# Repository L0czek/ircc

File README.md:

# Resonant Converter Controller

This repository contains a work-in-progress resonant converter controller project based on the STM32G474 microcontroller. The system splits responsibilities between the MCU (`controller`) and a host application (`host`) running on an x86 machine for configuration, logging, and waveform retrieval.

**Goals**
- Implement a phase-shifted resonant converter controller using the STM32G474 high-resolution timers.
- Provide over-current and other protections using built-in ADCs and comparator peripherals.
- Log waveforms to local SRAM for later retrieval by the host.
- Provide a PC-side host binary to configure and interact with the MCU.

Repository layout
- [controller](controller): MCU firmware (STM32 HAL-based). Core control logic lives here.
- [host](host): Host-side application that communicates with the MCU (x86 binary).
- [target](target): CubeMX / board-specific projects and HAL integration for different targets/boards.
- [pcb](pcb): KiCad PCB design files for the controller hardware.
- [protocol](protocol): Protocol definitions and protobufs used by host/MCU.
- [external](external): Third-party libraries and dependencies (e.g., nanpb, drivers).
- [build](build): Top-level build artifacts and CMake cache (generated during builds).

Quick start

Build host part (x86):

1. Enter the host directory and create a build directory:

```bash
cd host
mkdir -p build && cd build
cmake ..
make -j
```

The produced host binary will be in `host/build` (or as specified by the host CMakeLists).

Build MCU firmware:

1. Edit or inspect the CubeMX project in the appropriate `target/*` folder (for your chosen board). Generate code from CubeMX if you modify pin/peripheral configuration.
2. Use CMake from the top-level CMake to build the firmware. Example (from project root):

```bash
mkdir -p build-mcu && cd build-mcu
cmake -DCMAKE_TOOLCHAIN_FILE=cmake/gcc-arm-none-eabi.cmake ..
make -j
```

Flashing and debugging
- An OpenOCD config is available at `build/openocd.cfg` for target debugging.
- Typical workflow using the repository make targets:

	1. Start OpenOCD to provide the debug server:

		 ```bash
		 make openocd
		 ```

	2. In a separate terminal, flash or debug the firmware:

		 - To flash and run the firmware:

			 ```bash
			 make run
			 ```

		 - To spawn `gdb` for interactive debugging (connects to the OpenOCD server):

			 ```bash
			 make gdb
			 ```

- Or use your preferred OpenOCD/ST-Link workflow if you have a different setup.

Protocol and message formats
- Communication between host and MCU uses a UART serial link and the message definitions in the [protocol](protocol) directory (protobuf/nanopb). Regenerate or inspect generated code if you change `.proto` files.

Design notes
- The controller firmware uses the STM32G474 high-resolution timers to implement phase-shift control for MOSFET/IGBT bridge switching.
- ADCs, comparators, and timers are used for protections, sampling, and logging to SRAM.

Acknowledgements
- Third-party libraries are located in `external/` — see their respective LICENSE files for details.

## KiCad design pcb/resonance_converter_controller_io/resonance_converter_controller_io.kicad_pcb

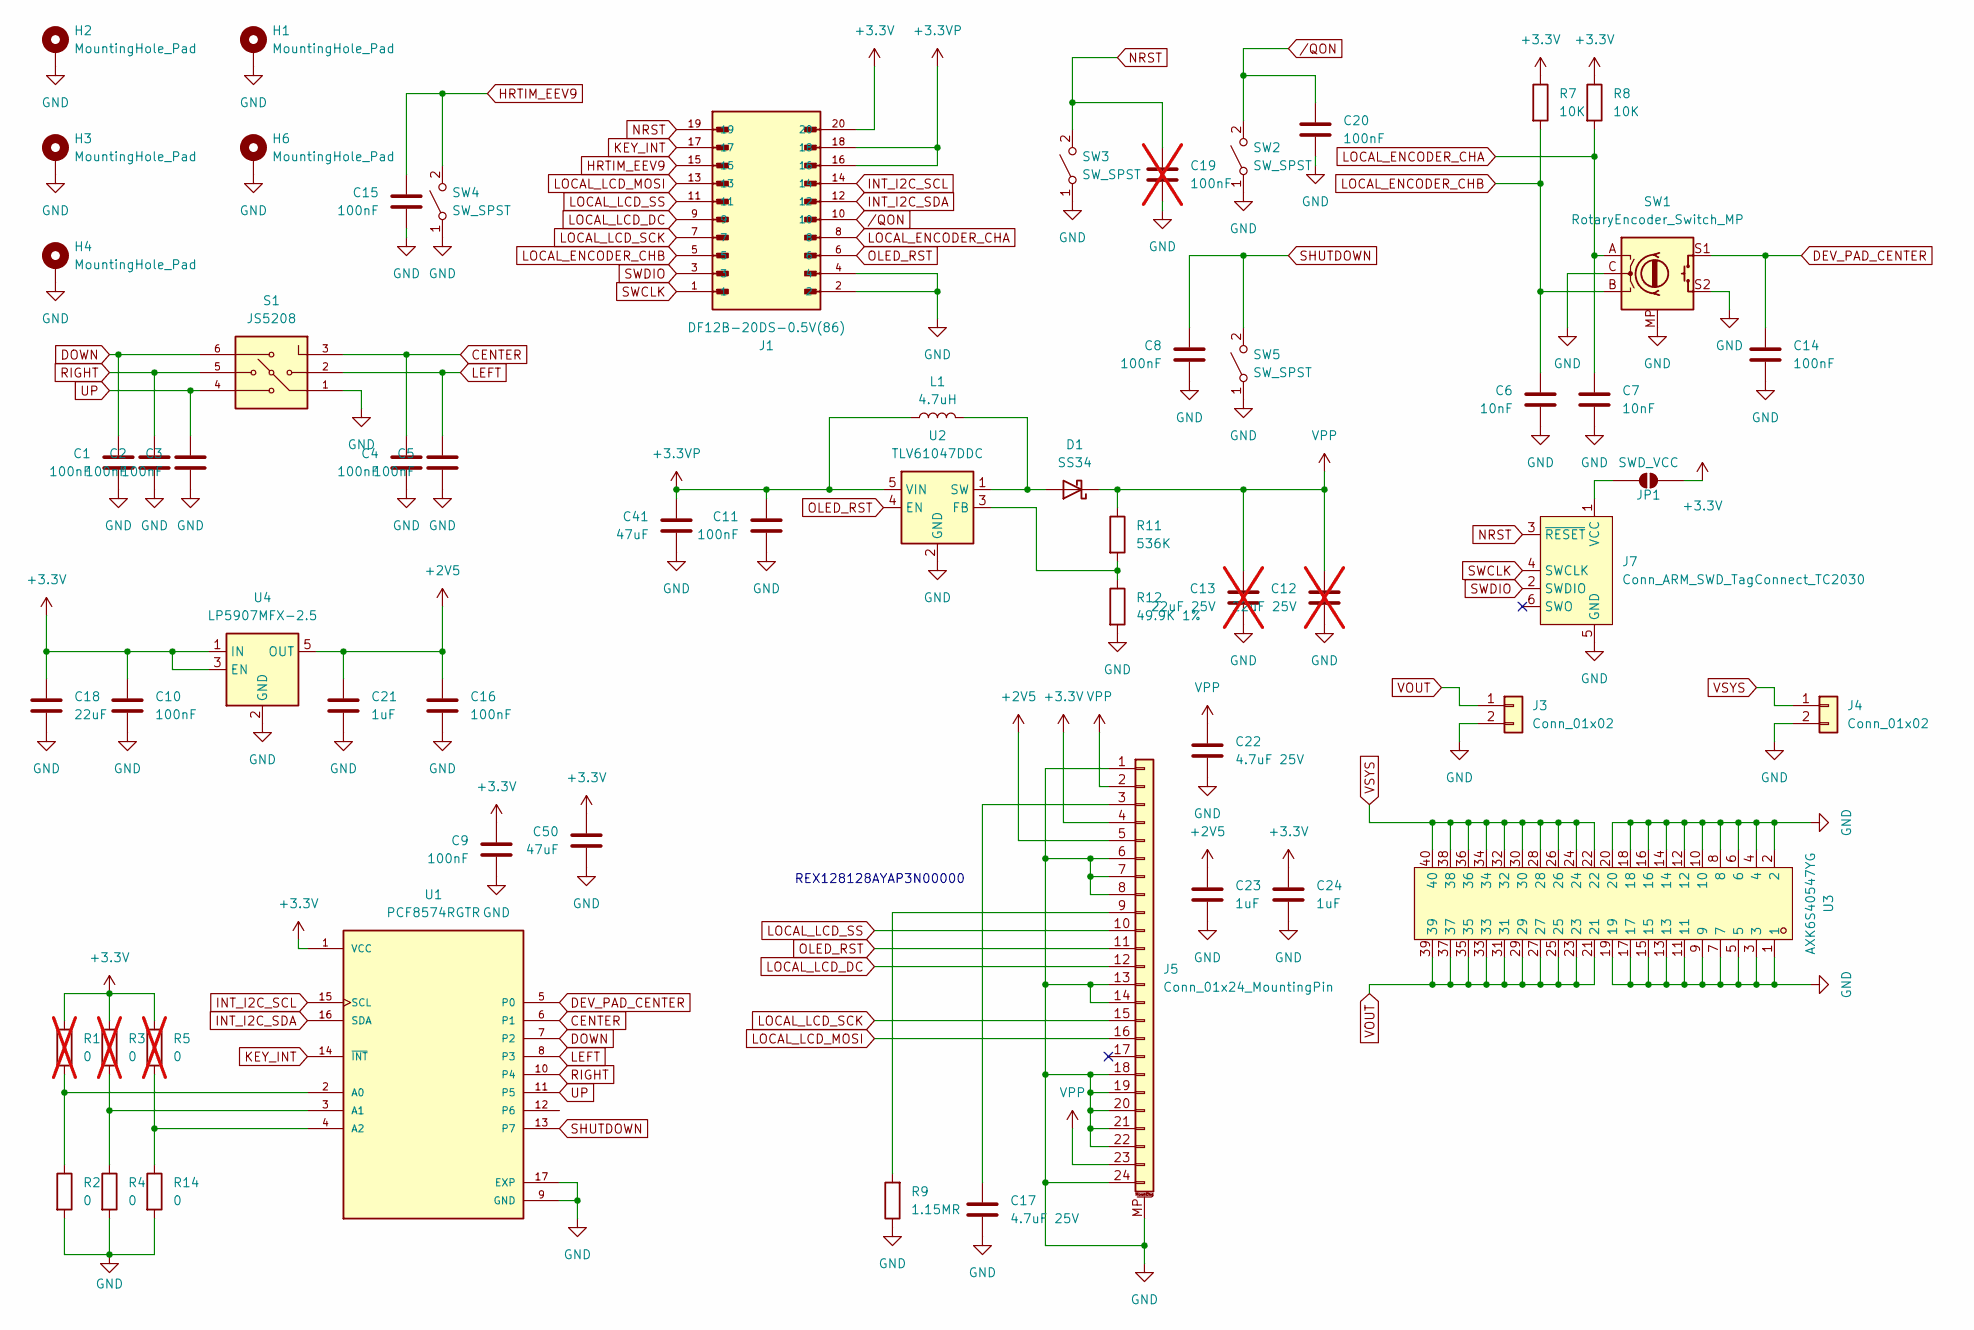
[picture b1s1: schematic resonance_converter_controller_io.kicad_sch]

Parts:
C1, C2, C3, C4, C5, C8, C9, C10, C11, C14, C15, C16, C20: 100nF; C_0402_1005Metric; LCSC Part C307331
C6, C7: 10nF; C_0402_1005Metric; LCSC Part C15195
C12, C13: 22uF 25V; C_1206_3216Metric; LCSC Part C12891; not fitted
C17, C22: 4.7uF 25V; C_0805_2012Metric; LCSC Part C1779
C18: 22uF; C_0805_2012Metric; LCSC Part C45783
C19: 100nF; C_0402_1005Metric; LCSC Part C307331; not fitted
C21: 1uF; C_0805_2012Metric; LCSC Part C28323
C23, C24: 1uF; C_0402_1005Metric; LCSC Part C52923
C41, C50: 47uF; C_1206_3216Metric; LCSC Part C96123
D1: SS34; D_SMA; MPN SS34; LCSC Part C8678
H1, H2, H3, H4, H6: MountingHole_Pad; MountingHole_2.2mm_M2_Pad_Via
J1: DF12B-20DS-0.5V(86); HRS_DF12B-20DS-0.5V_86_; MPN DF12B-20DS-0.5V(86)
J3, J4: Conn_01x02; PhoenixContact_MCV_1,5_2-G-3.5_1x02_P3.50mm_Vertical
J5: Conn_01x24_MountingPin; Hirose_FH12-24S-0.5SH_1x24-1MP_P0.50mm_Horizontal
J7: Conn_ARM_SWD_TagConnect_TC2030; Tag-Connect_TC2030-IDC-FP_2x03_P1.27mm_Vertical
JP1: SWD_VCC; SolderJumper-2_P1.3mm_Open_RoundedPad1.0x1.5mm
L1: 4.7uH; L_1210_3225Metric; MPN DFE322520FD-4R7M=P2; LCSC Part C2045343
R1, R3, R5: 0; R_0402_1005Metric; LCSC Part C17168; not fitted
R2, R4, R14: 0; R_0402_1005Metric; LCSC Part C17168
R7, R8: 10K; R_0402_1005Metric; LCSC Part C25744
R9: 1.15MR; R_0402_1005Metric
R11: 536K; R_0402_1005Metric
R12: 49.9K 1%; R_0402_1005Metric; LCSC Part C25897
S1: JS5208; SW_JS5208; PARTREV D; DigiKey_Part_Number EG4561-ND
SW1: RotaryEncoder_Switch_MP; RotaryEncoder_Alps_EC11E-Switch_Vertical_H20mm_MountingHoles
SW2, SW3, SW4, SW5: SW_SPST; SW_SPST_EVQPE1
U1: PCF8574RGTR; QFN50P300X300X100-17N; PARTREV J; DigiKey_Part_Number 296-21238-1-ND
U2: TLV61047DDC; SOT-23-5
U3: AXK6S40547YG; CONN-SMD_40P_AXK6S40547YG; MPN AXK6S40547YG; LCSC Part C6466627
U4: LP5907MFX-2.5; SOT-23-5

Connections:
+2V5: C16.1, C21.2, C23.1, J5.5, U4.5 (OUT)
+3.3V: C9.1, C10.1, C18.2, C24.1, C50.1, J1.20, J5.4, JP1.2 (B), R1.1, R3.1, R5.1, R7.1, R8.1, U1.1 (VCC), U4.1 (IN), U4.3 (EN)
+3.3VP: C11.1, C41.1, J1.16, J1.18, L1.1, U2.5 (VIN)
CENTER: C4.1, S1.3, U1.6 (P1)
DEV_PAD_CENTER: C14.1, SW1.S1, U1.5 (P0)
DOWN: C1.1, S1.6, U1.7 (P2)
GND: C1.2, C2.2, C3.2, C4.2, C5.2, C6.2, C7.2, C8.2, C9.2, C10.2, C11.2, C12.2, C13.2, C14.2, C15.2, C16.2, C17.1, C18.1, C19.2, C20.2, C21.1, C22.1, C23.2, C24.2, C41.2, C50.2, H1.1 (1_1), H2.1 (1_1), H3.1 (1_1), H4.1 (1_1), H6.1 (1_1), J1.2, J1.4, J3.2, J4.2, J5.1, J5.6, J5.7, J5.8, J5.13, J5.14, J5.18, J5.19, J5.20, J5.21, J5.22, J5.24, J5.MP (MountPin), J7.5 (GND), R2.2, R4.2, R9.1, R12.2, R14.2, S1.1, SW1.C, SW1.MP, SW1.S2, SW2.1 (A), SW3.1 (A), SW4.1 (A), SW5.1 (A), U1.9 (GND), U1.17 (EXP), U2.2 (GND), U3.1, U3.2, U3.3, U3.4, U3.5, U3.6, U3.7, U3.8, U3.9, U3.10, U3.11, U3.12, U3.13, U3.14, U3.15, U3.16, U3.17, U3.18, U3.19, U3.20, U4.2 (GND)
HRTIM_EEV9: C15.1, J1.15, SW4.2 (B)
INT_I2C_SCL: J1.14, U1.15 (SCL)
INT_I2C_SDA: J1.12, U1.16 (SDA)
KEY_INT: J1.17, U1.14 (~INT)
LEFT: C5.1, S1.2, U1.8 (P3)
LOCAL_ENCODER_CHA: C7.1, J1.8, R8.2, SW1.A
LOCAL_ENCODER_CHB: C6.1, J1.5, R7.2, SW1.B
LOCAL_LCD_DC: J1.9, J5.12
LOCAL_LCD_MOSI: J1.13, J5.16
LOCAL_LCD_SCK: J1.7, J5.15
LOCAL_LCD_SS: J1.11, J5.10
NRST: C19.1, J1.19, J7.3 (~RESET), SW3.2 (B)
unnamed: D1.2 (A), L1.2, U2.1 (SW)
unnamed: C17.2, J5.3
unnamed: J5.9, R9.2
unnamed: J7.1 (VCC), JP1.1 (A)
unnamed: R1.2, R2.1, U1.2 (A0)
unnamed: R3.2, R4.1, U1.3 (A1)
unnamed: R5.2, R14.1, U1.4 (A2)
unnamed: R11.2, R12.1, U2.3 (FB)
OLED_RST: J1.6, J5.11, U2.4 (EN)
RIGHT: C2.1, S1.5, U1.10 (P4)
SHUTDOWN: C8.1, SW5.2 (B), U1.13 (P7)
SWCLK: J1.1, J7.4 (SWCLK)
SWDIO: J1.3, J7.2 (SWDIO)
UP: C3.1, S1.4, U1.11 (P5)
VOUT: J3.1, U3.21, U3.23, U3.25, U3.27, U3.29, U3.31, U3.33, U3.35, U3.37, U3.39
VPP: C12.1, C13.1, C22.2, D1.1 (K), J5.2, J5.23, R11.1
VSYS: J4.1, U3.22, U3.24, U3.26, U3.28, U3.30, U3.32, U3.34, U3.36, U3.38, U3.40
/QON: C20.1, J1.10, SW2.2 (B)

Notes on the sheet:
REX128128AYAP3N00000

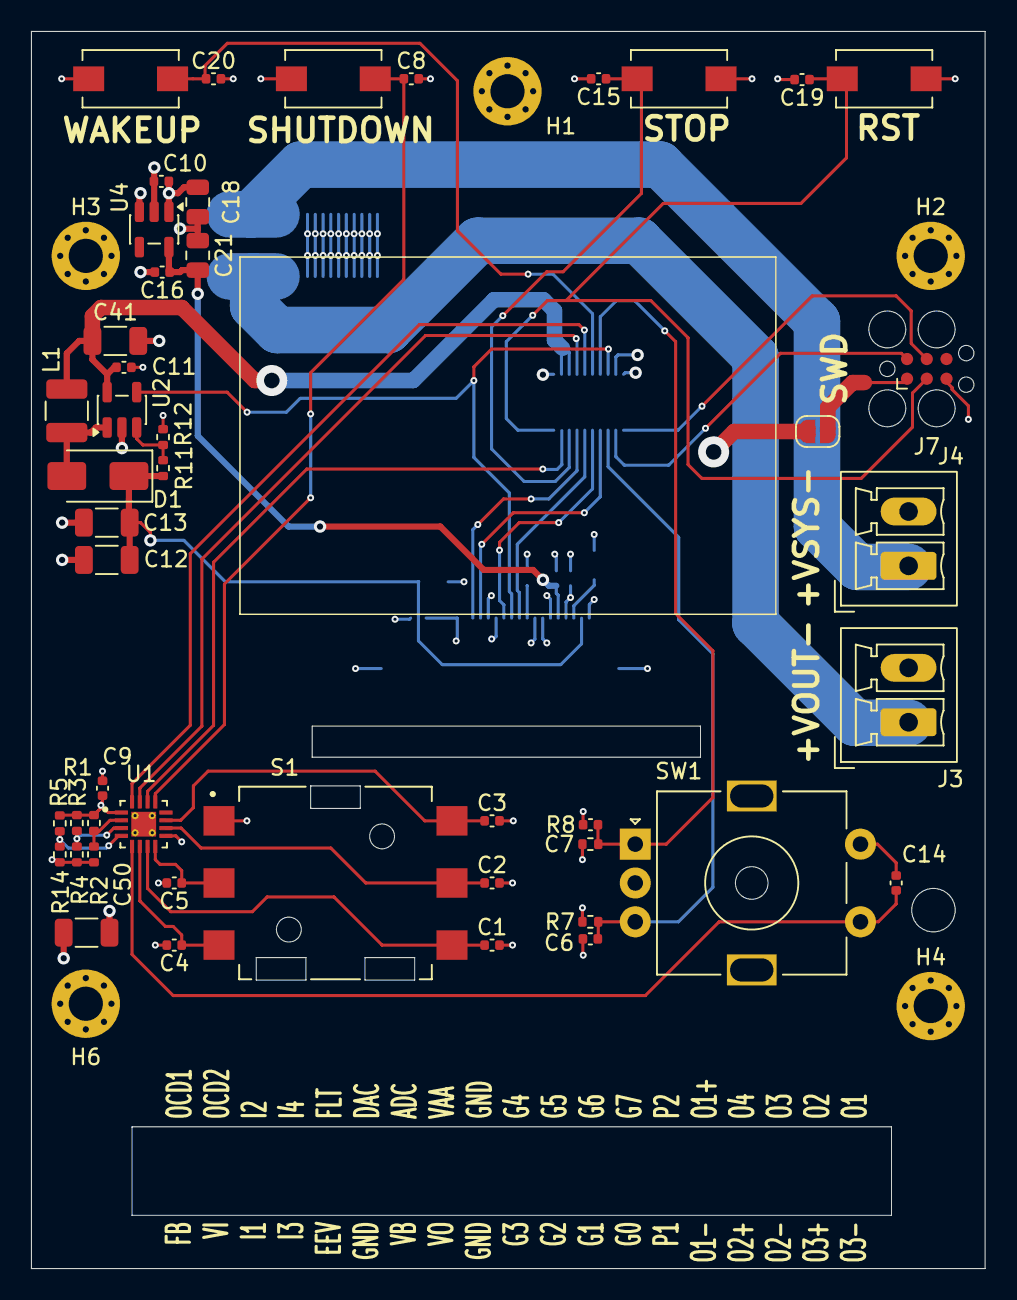
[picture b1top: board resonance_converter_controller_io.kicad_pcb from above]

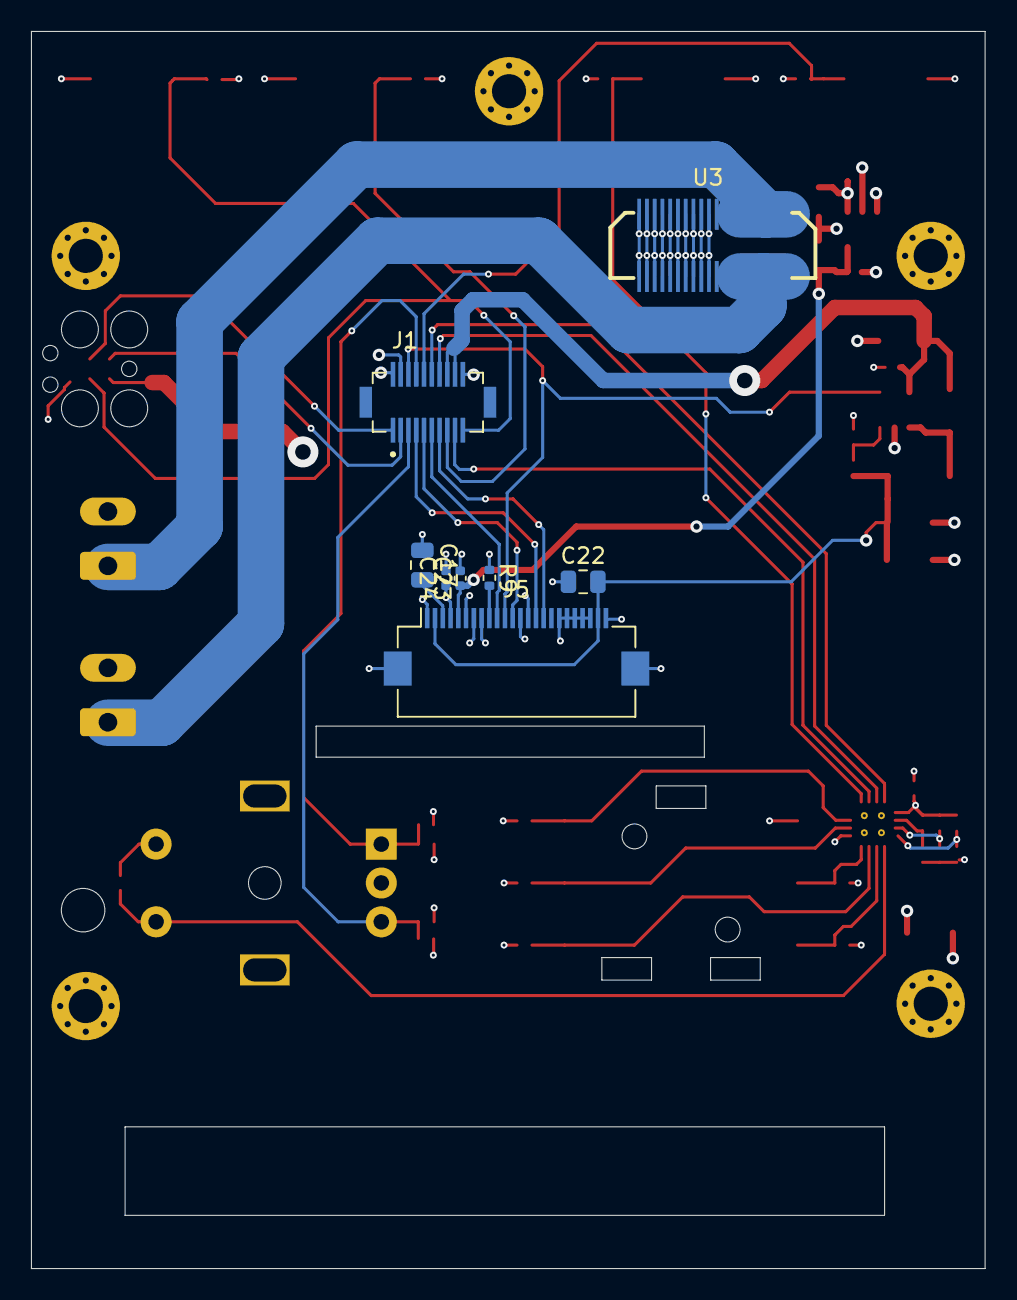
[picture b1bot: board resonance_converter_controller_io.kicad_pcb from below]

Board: 4 copper layers, 61.4 x 79.6 mm, 60 parts (8 on the bottom side), 37 nets.

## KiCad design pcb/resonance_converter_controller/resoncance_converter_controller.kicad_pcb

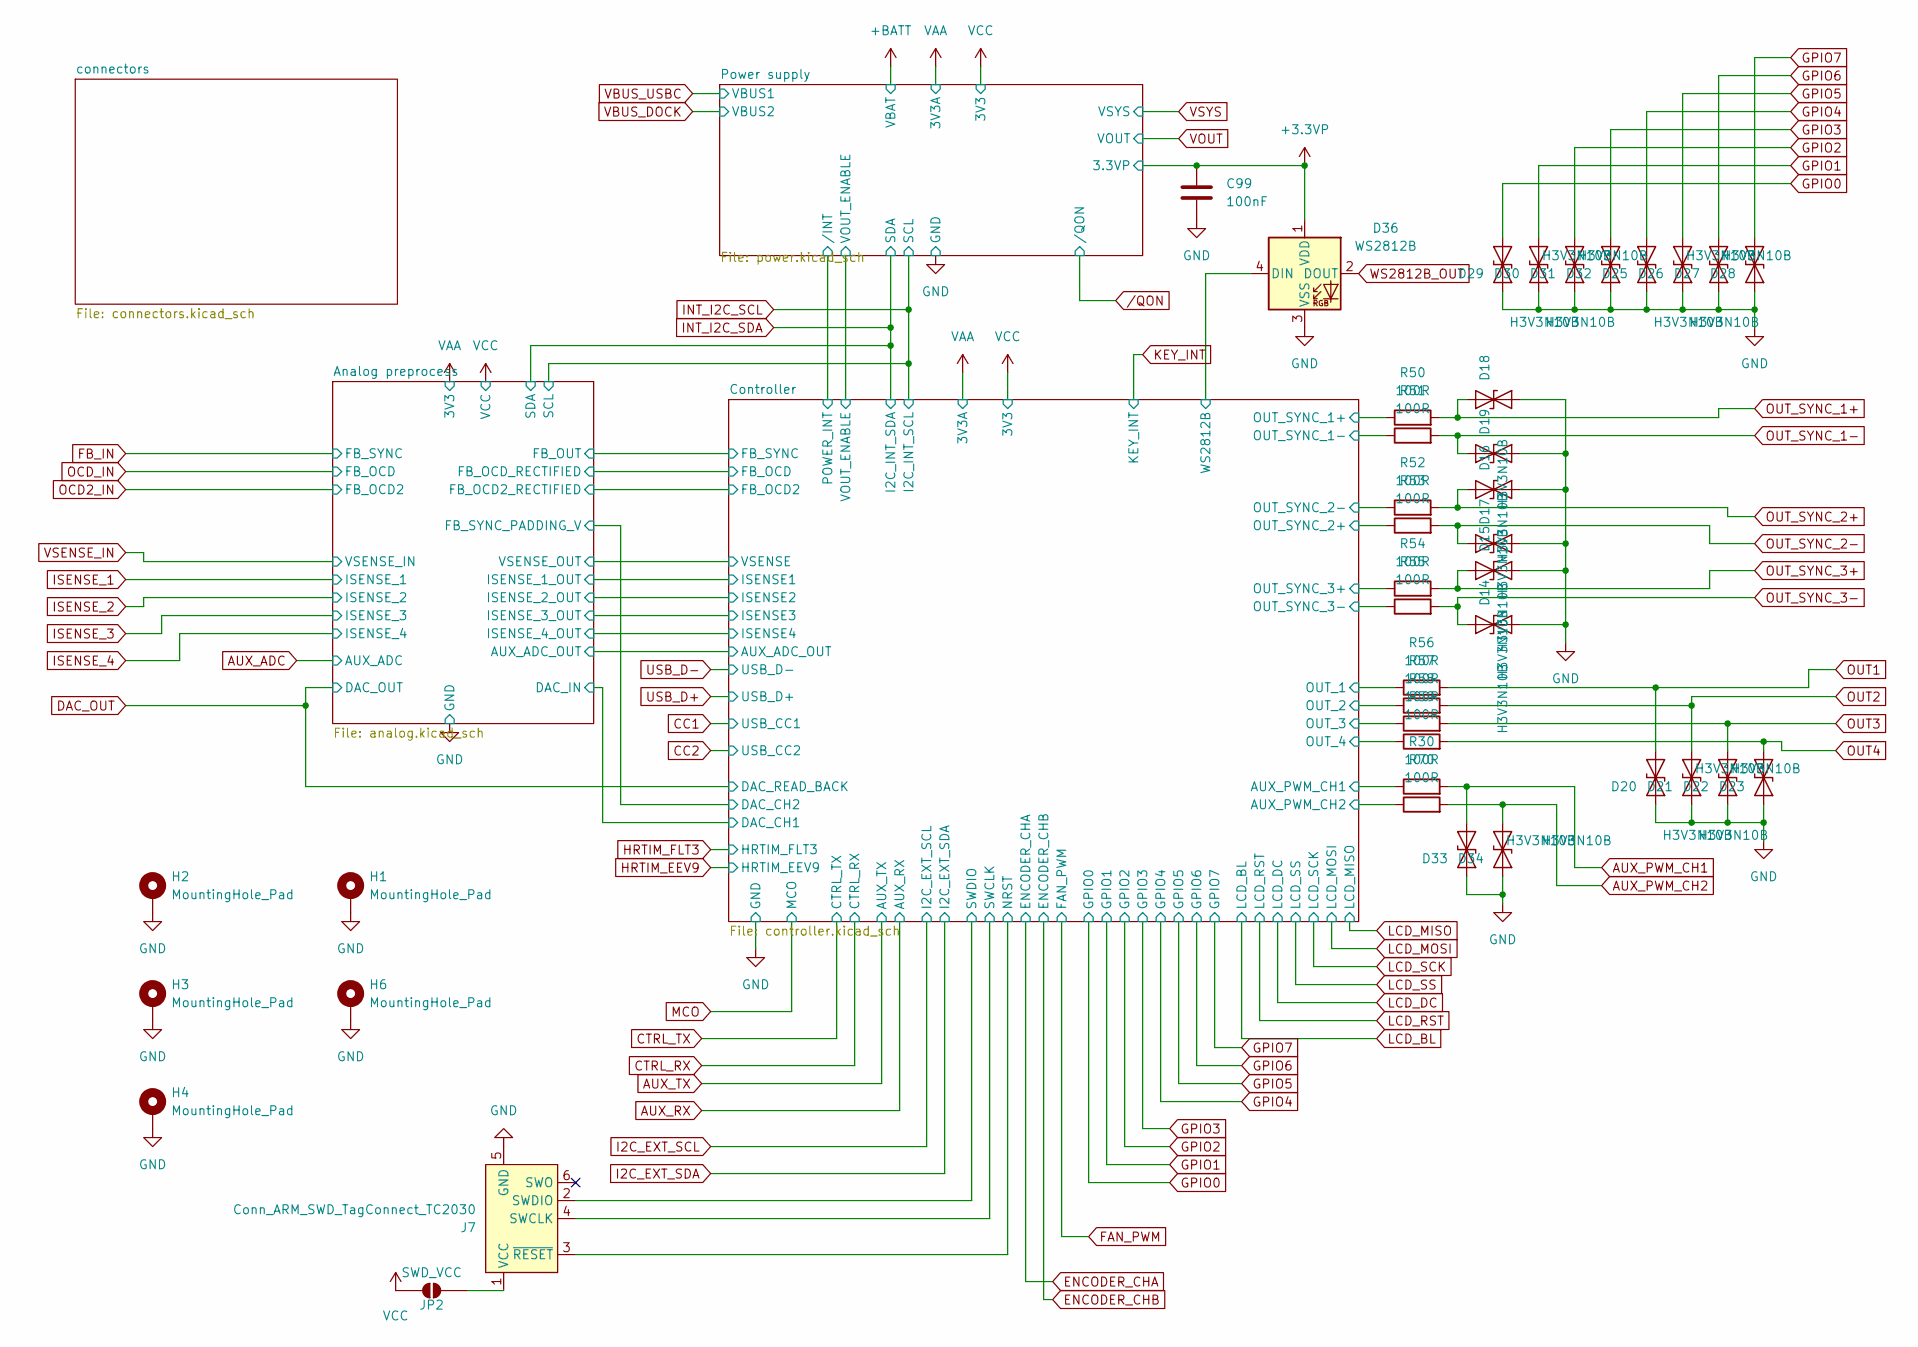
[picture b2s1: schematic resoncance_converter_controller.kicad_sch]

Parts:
C99: 100nF; C_0402_1005Metric; LCSC C307331
D14, D15, D16, D17, D18, D19, D20, D21, D22, D23, D25, D26, D27, D28, D29, D30, D31, D32, D33, D34: H3V3N10B; D_0402_1005Metric; LCSC C20617909
D36: WS2812B; LED_WS2812B-Mini_PLCC4_3.5x3.5mm
H1, H2, H3, H4, H6: MountingHole_Pad; MountingHole_2.2mm_M2_Pad_Via
J7: Conn_ARM_SWD_TagConnect_TC2030; Tag-Connect_TC2030-IDC-FP_2x03_P1.27mm_Vertical
JP2: SWD_VCC; SolderJumper-2_P1.3mm_Open_RoundedPad1.0x1.5mm
R30, R50, R51, R52, R53, R54, R55, R56, R57, R58, R59, R70: 100R; R_0402_1005Metric; LCSC C25076

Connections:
+3.3VP: C99.1, D36.1 (VDD); also elsewhere on the board
/Controller/AUX_PWM_CH1: R30.1; also elsewhere on the board
/Controller/AUX_PWM_CH2: R70.1; also elsewhere on the board
/Controller/OUT_1: R56.1; also elsewhere on the board
/Controller/OUT_2: R57.1; also elsewhere on the board
/Controller/OUT_3: R58.1; also elsewhere on the board
/Controller/OUT_4: R59.1; also elsewhere on the board
/Controller/OUT_SYNC_1+: R50.1; also elsewhere on the board
/Controller/OUT_SYNC_1-: R51.1; also elsewhere on the board
/Controller/OUT_SYNC_2+: R53.1; also elsewhere on the board
/Controller/OUT_SYNC_2-: R52.1; also elsewhere on the board
/Controller/OUT_SYNC_3+: R54.1; also elsewhere on the board
/Controller/OUT_SYNC_3-: R55.1; also elsewhere on the board
/Controller/WS2812B: D36.4 (DIN); also elsewhere on the board
AUX_PWM_CH1: D33.1 (A1), R30.2; also elsewhere on the board
AUX_PWM_CH2: D34.1 (A1), R70.2; also elsewhere on the board
GND: C99.2, D14.1 (A1), D15.1 (A1), D16.1 (A1), D17.1 (A1), D18.1 (A1), D19.1 (A1), D20.2 (A2), D21.2 (A2), D22.2 (A2), D23.2 (A2), D25.2 (A2), D26.2 (A2), D27.2 (A2), D28.2 (A2), D29.2 (A2), D30.2 (A2), D31.2 (A2), D32.2 (A2), D33.2 (A2), D34.2 (A2), D36.3 (VSS), H1.1 (1_1), H2.1 (1_1), H3.1 (1_1), H4.1 (1_1), H6.1 (1_1), J7.5 (GND); also elsewhere on the board
GPIO0: D29.1 (A1); also elsewhere on the board
GPIO1: D30.1 (A1); also elsewhere on the board
GPIO2: D31.1 (A1); also elsewhere on the board
GPIO3: D32.1 (A1); also elsewhere on the board
GPIO4: D25.1 (A1); also elsewhere on the board
GPIO5: D26.1 (A1); also elsewhere on the board
GPIO6: D27.1 (A1); also elsewhere on the board
GPIO7: D28.1 (A1); also elsewhere on the board
NRST: J7.3 (~RESET); also elsewhere on the board
unnamed: J7.1 (VCC), JP2.2 (B)
OUT1: D20.1 (A1), R56.2; also elsewhere on the board
OUT2: D21.1 (A1), R57.2; also elsewhere on the board
OUT3: D22.1 (A1), R58.2; also elsewhere on the board
OUT4: D23.1 (A1), R59.2; also elsewhere on the board
OUT_SYNC_1+: D18.2 (A2), R50.2; also elsewhere on the board
OUT_SYNC_1-: D19.2 (A2), R51.2; also elsewhere on the board
OUT_SYNC_2+: D16.2 (A2), R52.2; also elsewhere on the board
OUT_SYNC_2-: D17.2 (A2), R53.2; also elsewhere on the board
OUT_SYNC_3+: D15.2 (A2), R54.2; also elsewhere on the board
OUT_SYNC_3-: D14.2 (A2), R55.2; also elsewhere on the board
SWCLK: J7.4 (SWCLK); also elsewhere on the board
SWDIO: J7.2 (SWDIO); also elsewhere on the board
VCC: JP2.1 (A); also elsewhere on the board
WS2812B_OUT: D36.2 (DOUT); also elsewhere on the board

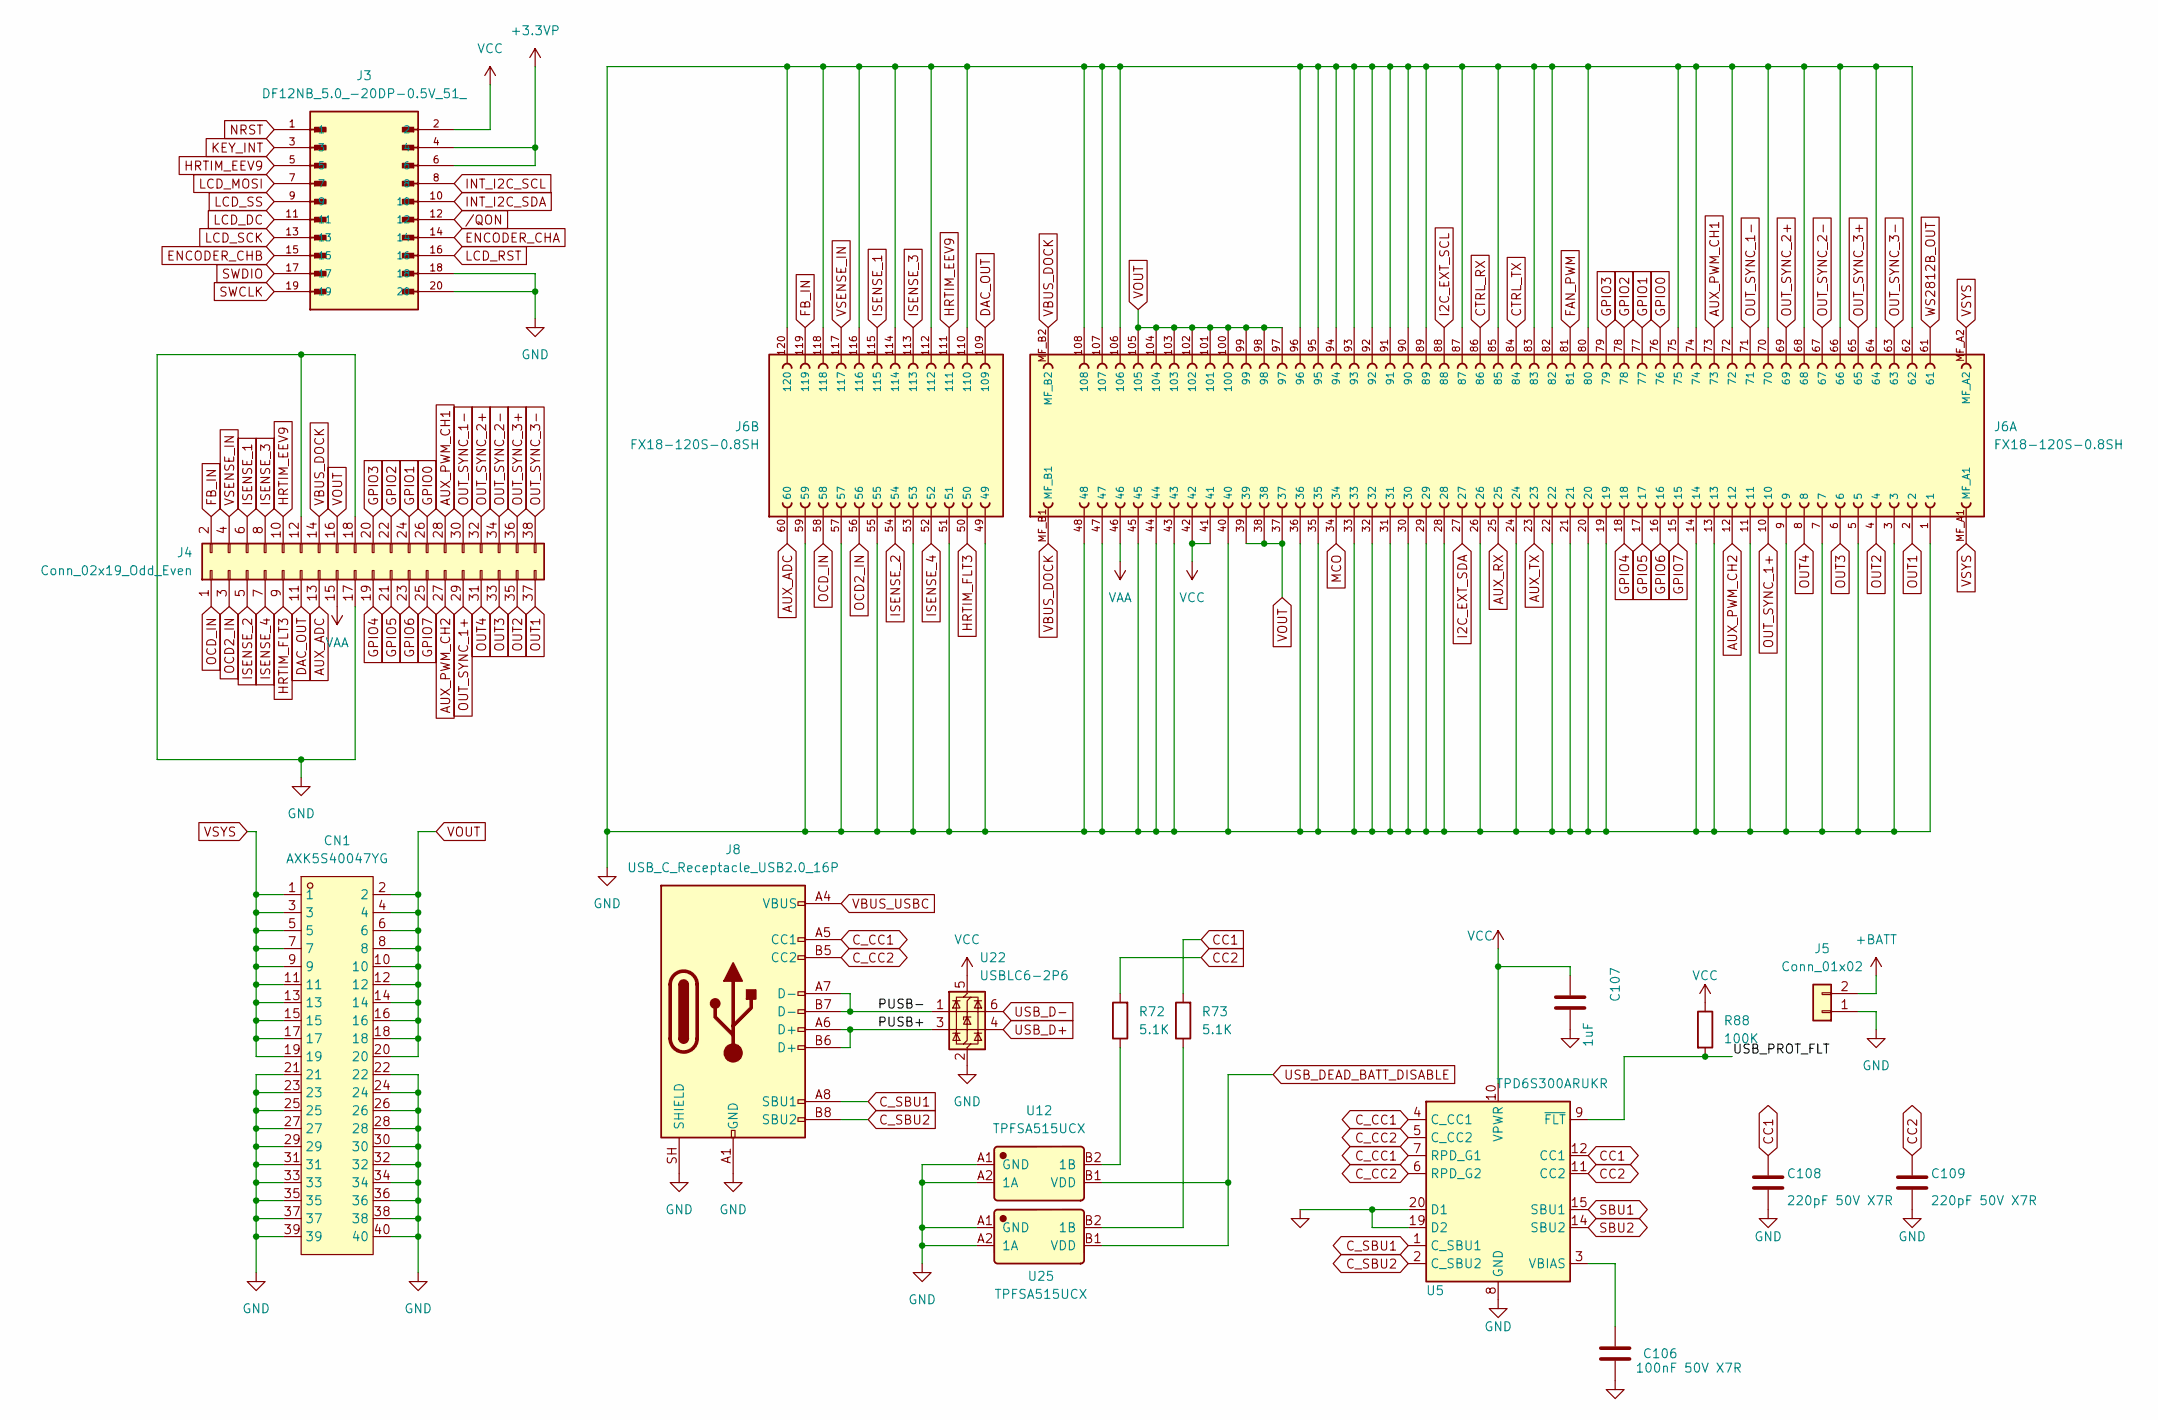
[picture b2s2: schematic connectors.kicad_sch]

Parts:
C106: 100nF 50V X7R; C_0603_1608Metric; LCSC C14663
C107: 1uF; C_0402_1005Metric; LCSC C52923
C108, C109: 220pF 50V X7R; C_0402_1005Metric; LCSC C1530
CN1: AXK5S40047YG; CONN-SMD_40P-P0.50_AXK5S40047YG; LCSC Part C3647996
J3: DF12NB_5.0_-20DP-0.5V_51_; HRS_DF12NB_5.0_-20DP-0.5V_51_
J4: Conn_02x19_Odd_Even; PinSocket_2x19_P2.54mm_Vertical_SMD
J5: Conn_01x02; AMASS_XT30U-M_1x02_P5.0mm_Vertical
J6: FX18-120S-0.8SH; HIROSE_FX18-120S-0.8SH; PARTREV 1
J8: USB_C_Receptacle_USB2.0_16P; USB_C_Receptacle_GCT_USB4105-xx-A_16P_TopMnt_Horizontal
R72, R73: 5.1K; R_0402_1005Metric; LCSC C25905
R88: 100K; R_0402_1005Metric; LCSC C25741
U5: TPD6S300ARUKR; Texas_RUK0020B_WQFN-20-1EP_3x3mm_P0.4mm_EP1.7x1.7mm_Thermal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
U12, U25: TPFSA515UCX; Manufacturer Part TPFSA515UCX; LCSC C52145990
U22: USBLC6-2P6; SOT-666

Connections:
+3.3VP: J3.4, J3.6; also elsewhere on the board
+BATT: J5.2; also elsewhere on the board
/connectors/PUSB+: J8.A6 (D+), J8.B6 (D+), U22.3 (I/O2)
/connectors/PUSB-: J8.A7 (D-), J8.B7 (D-), U22.1 (I/O1)
/connectors/USB_PROT_FLT: R88.2, U5.9 (~FLT)
AUX_ADC: J4.13, J6.60; also elsewhere on the board
AUX_PWM_CH1: J4.28, J6.73; also elsewhere on the board
AUX_PWM_CH2: J4.27, J6.12; also elsewhere on the board
AUX_RX: J6.25; also elsewhere on the board
AUX_TX: J6.23; also elsewhere on the board
CC1: C108.1, R73.2, U5.12 (CC1); also elsewhere on the board
CC2: C109.1, R72.2, U5.11 (CC2); also elsewhere on the board
CTRL_RX: J6.86; also elsewhere on the board
CTRL_TX: J6.84; also elsewhere on the board
C_CC1: J8.A5 (CC1), U5.4 (C_CC1), U5.7 (RPD_G1)
C_CC2: J8.B5 (CC2), U5.5 (C_CC2), U5.6 (RPD_G2)
C_SBU1: J8.A8 (SBU1), U5.1 (C_SBU1)
C_SBU2: J8.B8 (SBU2), U5.2 (C_SBU2)
DAC_OUT: J4.11, J6.109; also elsewhere on the board
ENCODER_CHA: J3.14; also elsewhere on the board
ENCODER_CHB: J3.15; also elsewhere on the board
FAN_PWM: J6.81; also elsewhere on the board
FB_IN: J4.2, J6.119; also elsewhere on the board
GND: C106.2, C107.2, C108.2, C109.2, CN1.21, CN1.22, CN1.23, CN1.24, CN1.25, CN1.26, CN1.27, CN1.28, CN1.29, CN1.30, CN1.31, CN1.32, CN1.33, CN1.34, CN1.35, CN1.36, CN1.37, CN1.38, CN1.39, CN1.40, J3.18, J3.20, J4.12, J4.17, J4.18, J5.1, J6.1, J6.3, J6.5, J6.7, J6.9, J6.11, J6.13, J6.14, J6.19, J6.20, J6.21, J6.22, J6.24, J6.26, J6.28, J6.29, J6.30, J6.31, J6.32, J6.33, J6.35, J6.36, J6.40, J6.43, J6.44, J6.45, J6.47, J6.48, J6.49, J6.51, J6.53, J6.55, J6.57, J6.59, J6.62, J6.64, J6.66, J6.68, J6.70, J6.72, J6.74, J6.75, J6.80, J6.82, J6.83, J6.85, J6.87, J6.89, J6.90, J6.91, J6.92, J6.93, J6.94, J6.95, J6.96, J6.106, J6.107, J6.108, J6.110, J6.112, J6.114, J6.116, J6.118, J6.120, J8.A1 (GND), J8.A12 (GND), J8.B1 (GND), J8.B12 (GND), J8.SH (SHIELD), U5.8 (GND), U5.13 (GND), U5.16 (GND), U5.17 (GND), U5.18 (GND), U5.19 (D2), U5.20 (D1), U5.21 (GND), U12.A1 (GND), U12.A2 (1A), U22.2 (GND), U25.A1 (GND), U25.A2 (1A); also elsewhere on the board
GPIO0: J4.26, J6.76; also elsewhere on the board
GPIO1: J4.24, J6.77; also elsewhere on the board
GPIO2: J4.22, J6.78; also elsewhere on the board
GPIO3: J4.20, J6.79; also elsewhere on the board
GPIO4: J4.19, J6.18; also elsewhere on the board
GPIO5: J4.21, J6.17; also elsewhere on the board
GPIO6: J4.23, J6.16; also elsewhere on the board
GPIO7: J4.25, J6.15; also elsewhere on the board
HRTIM_EEV9: J3.5, J4.10, J6.111; also elsewhere on the board
HRTIM_FLT3: J4.9, J6.50; also elsewhere on the board
I2C_EXT_SCL: J6.88; also elsewhere on the board
I2C_EXT_SDA: J6.27; also elsewhere on the board
INT_I2C_SCL: J3.8; also elsewhere on the board
INT_I2C_SDA: J3.10; also elsewhere on the board
ISENSE_1: J4.6, J6.115; also elsewhere on the board
ISENSE_2: J4.5, J6.54; also elsewhere on the board
ISENSE_3: J4.8, J6.113; also elsewhere on the board
ISENSE_4: J4.7, J6.52; also elsewhere on the board
KEY_INT: J3.3; also elsewhere on the board
LCD_DC: J3.11; also elsewhere on the board
LCD_MOSI: J3.7; also elsewhere on the board
LCD_RST: J3.16; also elsewhere on the board
LCD_SCK: J3.13; also elsewhere on the board
LCD_SS: J3.9; also elsewhere on the board
MCO: J6.34; also elsewhere on the board
NRST: J3.1; also elsewhere on the board
unnamed: C106.1, U5.3 (VBIAS)
unnamed: R72.1, U12.B2 (1B)
unnamed: R73.1, U25.B2 (1B)
OCD2_IN: J4.3, J6.56; also elsewhere on the board
OCD_IN: J4.1, J6.58; also elsewhere on the board
OUT1: J4.37, J6.2; also elsewhere on the board
OUT2: J4.35, J6.4; also elsewhere on the board
OUT3: J4.33, J6.6; also elsewhere on the board
OUT4: J4.31, J6.8; also elsewhere on the board
OUT_SYNC_1+: J4.29, J6.10; also elsewhere on the board
OUT_SYNC_1-: J4.30, J6.71; also elsewhere on the board
OUT_SYNC_2+: J4.32, J6.69; also elsewhere on the board
OUT_SYNC_2-: J4.34, J6.67; also elsewhere on the board
OUT_SYNC_3+: J4.36, J6.65; also elsewhere on the board
OUT_SYNC_3-: J4.38, J6.63; also elsewhere on the board
SBU1: U5.15 (SBU1); also elsewhere on the board
SBU2: U5.14 (SBU2); also elsewhere on the board
SWCLK: J3.19; also elsewhere on the board
SWDIO: J3.17; also elsewhere on the board
USB_D+: U22.4 (I/O2); also elsewhere on the board
USB_D-: U22.6 (I/O1); also elsewhere on the board
USB_DEAD_BATT_DISABLE: U12.B1 (VDD), U25.B1 (VDD); also elsewhere on the board
VAA: J4.15, J6.46; also elsewhere on the board
VBUS_DOCK: J4.14, J6.MF_B1, J6.MF_B2; also elsewhere on the board
VBUS_USBC: J8.A4 (VBUS), J8.A9 (VBUS), J8.B4 (VBUS), J8.B9 (VBUS); also elsewhere on the board
VCC: C107.1, J3.2, J6.41, J6.42, R88.1, U5.10 (VPWR), U22.5 (VBUS); also elsewhere on the board
VOUT: CN1.2, CN1.4, CN1.6, CN1.8, CN1.10, CN1.12, CN1.14, CN1.16, CN1.18, CN1.20, J4.16, J6.37, J6.38, J6.39, J6.97, J6.98, J6.99, J6.100, J6.101, J6.102, J6.103, J6.104, J6.105; also elsewhere on the board
VSENSE_IN: J4.4, J6.117; also elsewhere on the board
VSYS: CN1.1, CN1.3, CN1.5, CN1.7, CN1.9, CN1.11, CN1.13, CN1.15, CN1.17, CN1.19, J6.MF_A1, J6.MF_A2; also elsewhere on the board
WS2812B_OUT: J6.61; also elsewhere on the board
/QON: J3.12; also elsewhere on the board
